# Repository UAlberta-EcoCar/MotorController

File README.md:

# MotorController
## gitignore
* Ignoring board, schematic files

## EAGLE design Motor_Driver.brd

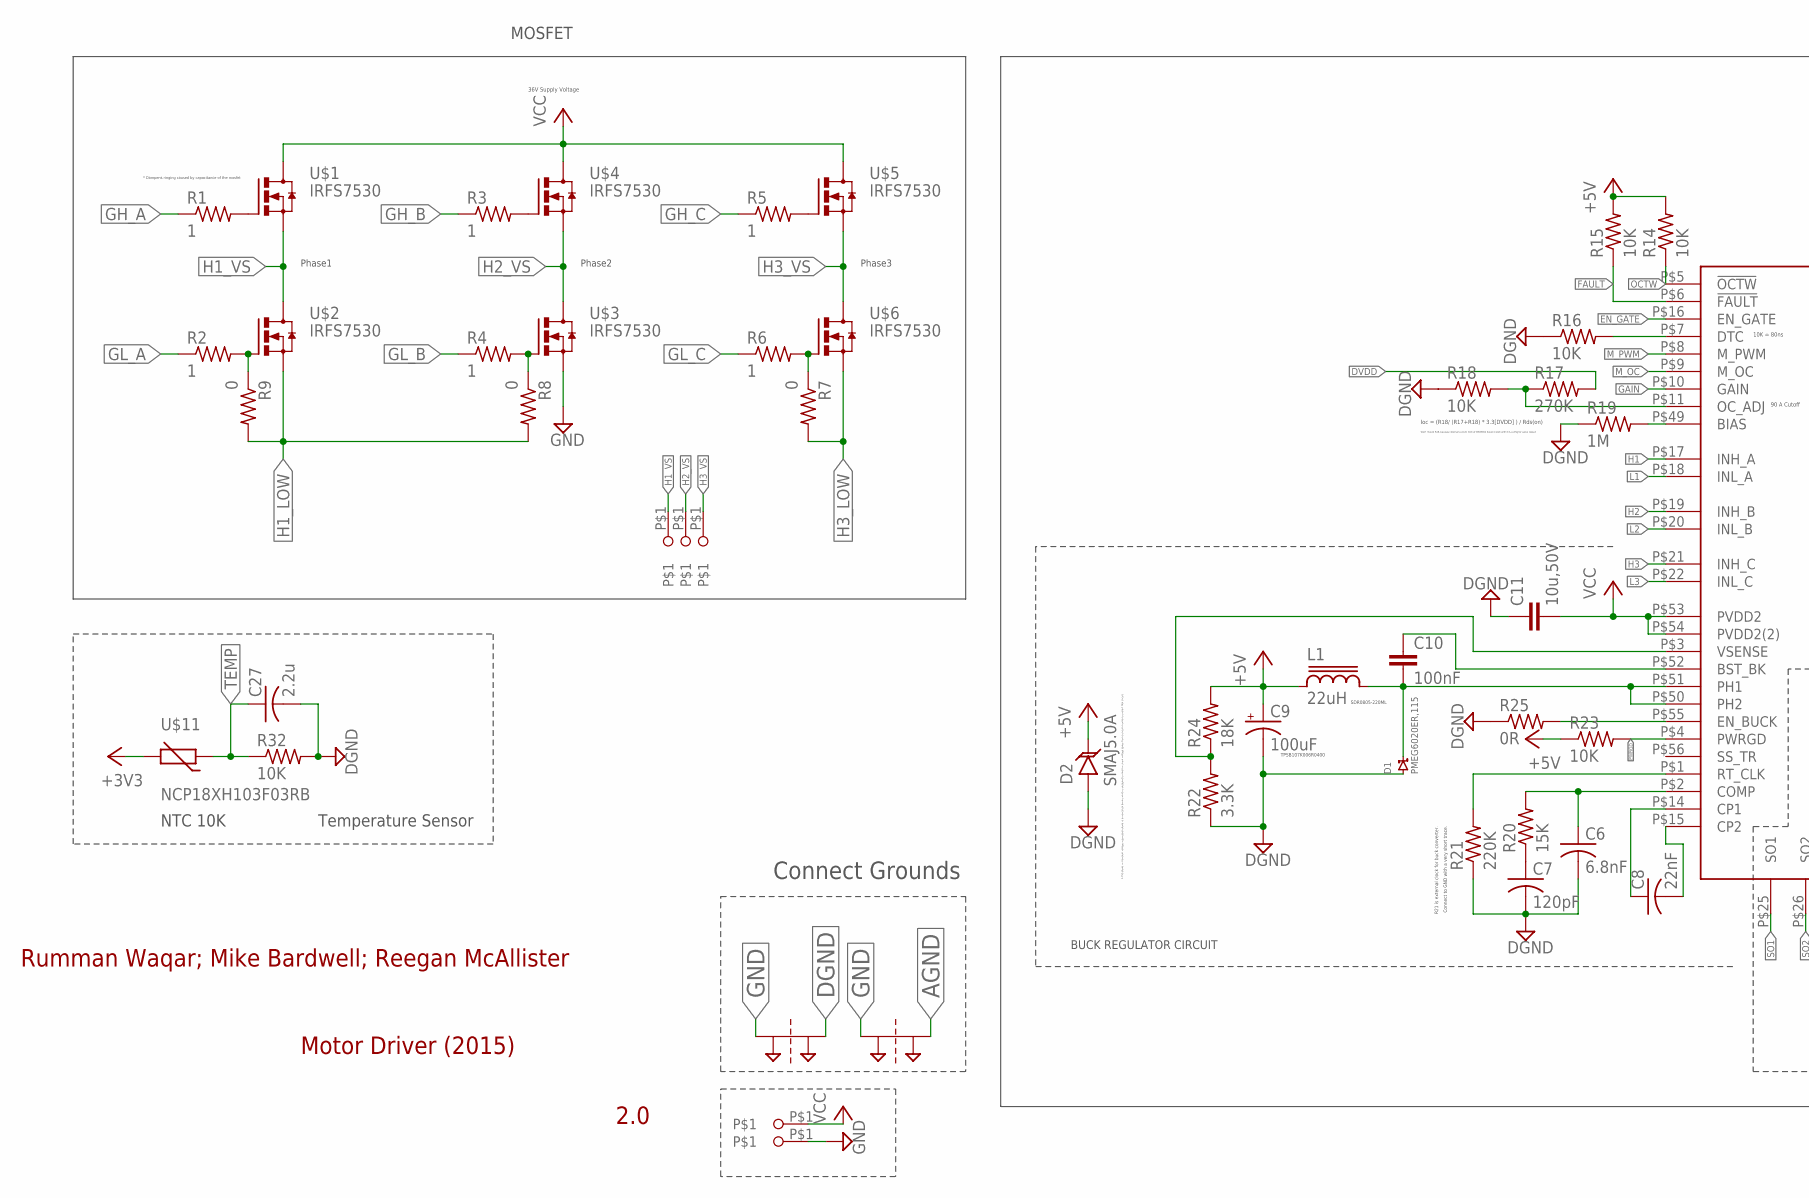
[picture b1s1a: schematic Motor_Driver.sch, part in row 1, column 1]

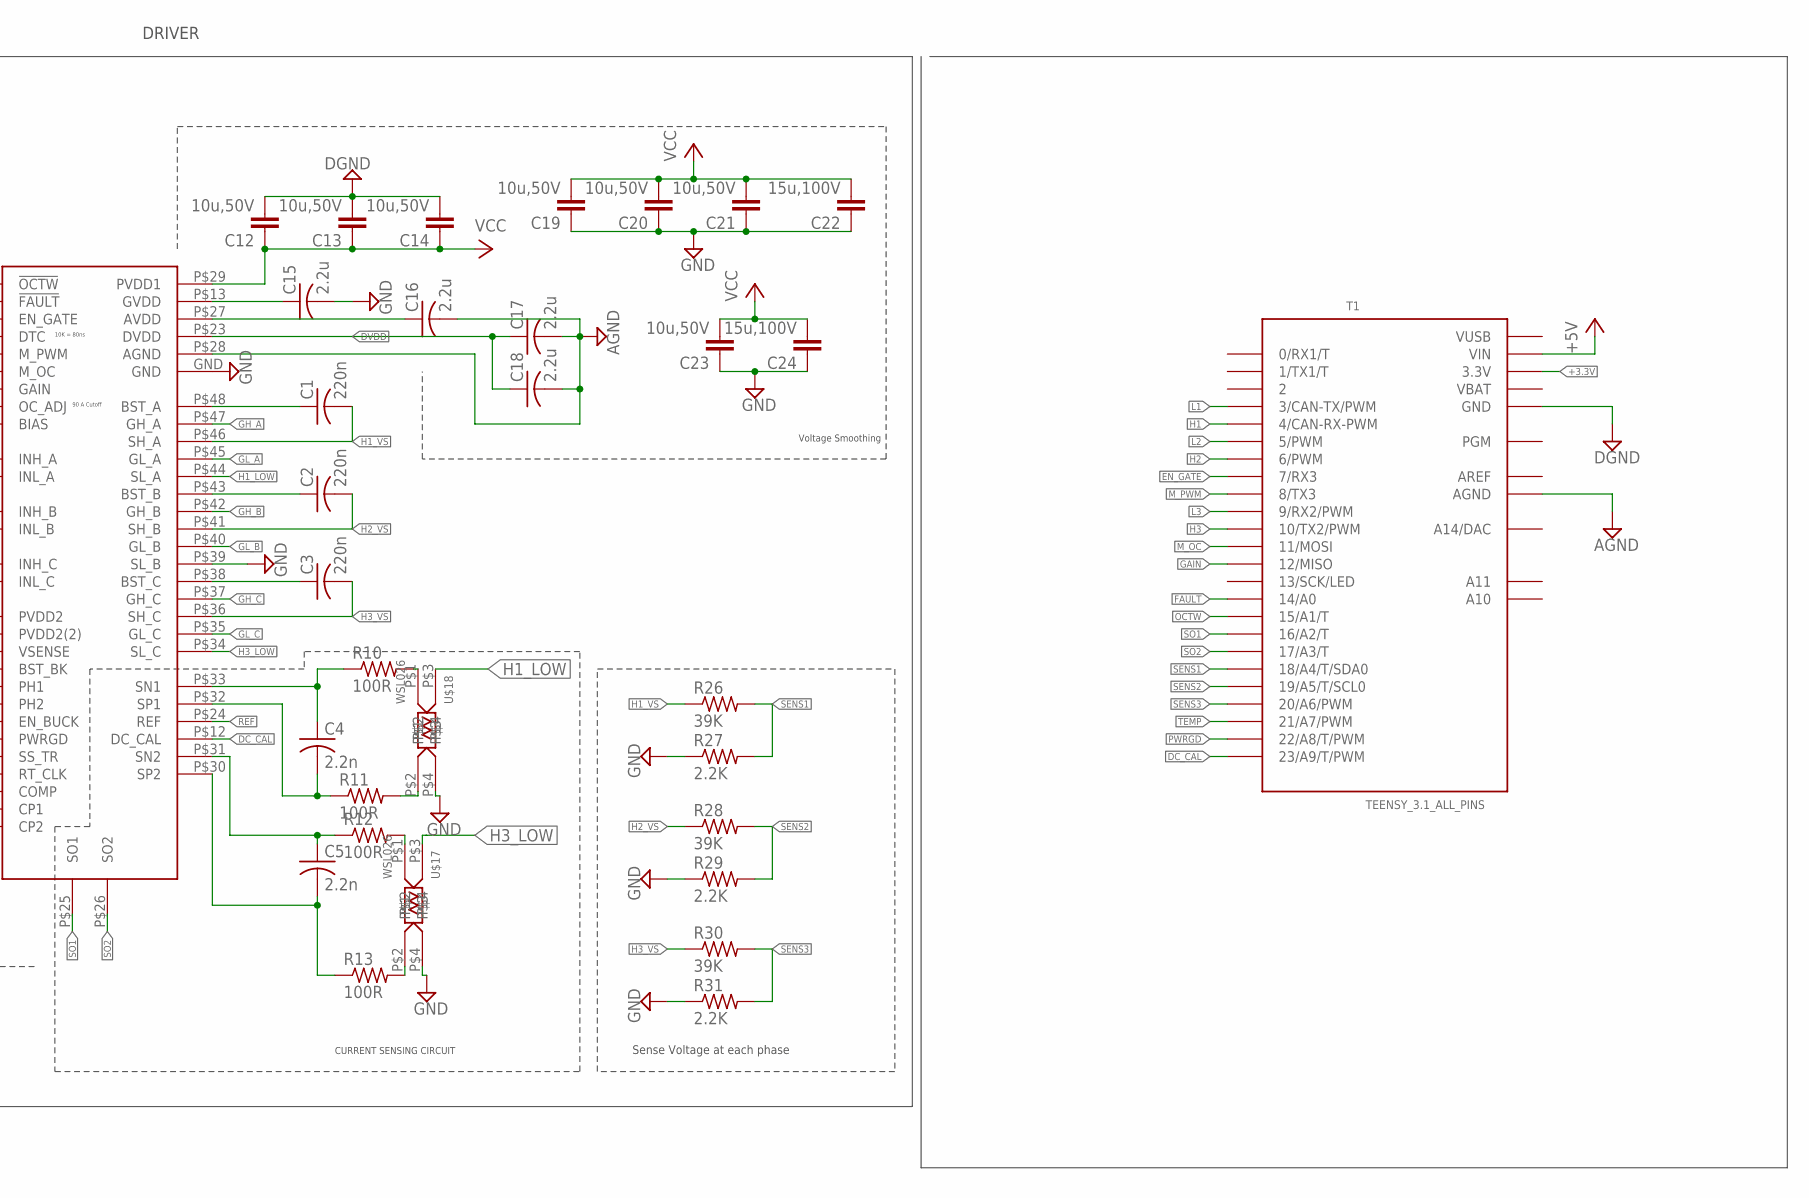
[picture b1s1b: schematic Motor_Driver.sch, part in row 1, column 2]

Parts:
C1, C2, C3: 220n; C0805
C4, C5: 2.2n; C0603
C6: 6.8nF; C0603
C7: 120pF; C0603
C8: 22nF; C0603
C9: 100uF; EIA3528-KIT
C10: 100nF; 0805
C11, C12, C13, C14, C19, C20, C21, C23: 10u,50V; 1206
C15, C16, C17, C18, C27: 2.2u; C0805
C22, C24: 15u,100V; C2220K
D1: PMEG6020ER,115; SOD123W
D2: SMAJ5.0A; SMA-DIODE
L1: 22uH; SDR0805
PT1, PT2: 2PT_GND_TIE
R1, R2, R3, R4, R5, R6: 1; R0603
R7, R8, R9: 0; R0603
R10, R11, R12, R13: 100R; R0603
R14, R15, R16, R18, R23: 10K; R0603
R17: 270K; R0603
R19: 1M; R0603
R20: 15K; R0603
R21: 220K; R0603
R22: 3.3K; R0603
R24: 18K; R0603
R25: 0R; R0603
R26, R28, R30: 39K; R0805
R27, R29, R31: 2.2K; R0805
R32: 10K; M0805
T1: TEENSY_3.1_ALL_PINS; TEENSY3-ALL_PINS
U$1, U$2, U$3, U$4, U$5, U$6: IRFS7530; IRF7530_HEATSINK
U$7: DRV8302
U$11: NCP18XH103F03RB; R0603
U$12, U$13, U$14, U$15, U$16: 1CONN_SOLDER; 1CONN_PAD
U$17, U$18: WSL026; REEL

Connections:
+3.3V: T1.3.3V, T1.3.3V1 (3.3V)
+3V3: U$11.2
+5V: C9.A (+), D2.C, L1.1, R14.2, R15.2, R23.1, R24.2, T1.VIN
AGND: C16.2, C17.2, C18.2, PT2.P$2, T1.AGND, U$7.P$28 (AGND)
AREF: T1.AREF
DC_CAL: T1.23/A9 (23/A9/T/PWM), U$7.P$12 (DC_CAL)
DGND: C6.2, C7.2, C9.C (-), C11.1, C12.2, C13.2, C14.2, C27.2, D1.P$1 (1), D2.A, PT1.P$2, R16.1, R18.1, R19.1, R21.1, R22.1, R25.1, R32.2, T1.GND, T1.GND1 (GND)
DVDD: C17.1, C18.1, R17.2, U$7.P$23 (DVDD)
EN_GATE: T1.7 (7/RX3), U$7.P$16 (EN_GATE)
FAULT: R15.1, T1.14/A0, U$7.P$6 (!FAULT)
GAIN: T1.12 (12/MISO), U$7.P$10 (GAIN)
GH_A: R1.1, U$7.P$47 (GH_A)
GH_B: R3.1, U$7.P$42 (GH_B)
GH_C: R5.1, U$7.P$37 (GH_C)
GL_A: R2.1, U$7.P$45 (GL_A)
GL_B: R4.1, U$7.P$40 (GL_B)
GL_C: R6.1, U$7.P$35 (GL_C)
GND: C15.2, C19.1, C20.1, C21.1, C22.1, C23.1, C24.1, PT1.P$1, PT2.P$1, R27.1, R29.1, R31.1, U$3.S1 (S), U$3.S2 (S), U$3.S3 (S), U$3.S4 (S), U$3.S5 (S), U$7.GND, U$7.P$39 (SL_B), U$16.P$1, U$17.P$4, U$18.P$4
H1: T1.4 (4/CAN-RX-PWM), U$7.P$17 (INH_A)
H1_LOW: R8.2, R9.2, U$2.S1 (S), U$2.S2 (S), U$2.S3 (S), U$2.S4 (S), U$2.S5 (S), U$7.P$44 (SL_A), U$18.P$3
H1_VS: C1.2, R26.1, U$1.S1 (S), U$1.S2 (S), U$1.S3 (S), U$1.S4 (S), U$1.S5 (S), U$2.D1 (D), U$7.P$46 (SH_A), U$14.P$1
H2: T1.6 (6/PWM), U$7.P$19 (INH_B)
H2_VS: C2.2, R28.1, U$3.D1 (D), U$4.S1 (S), U$4.S2 (S), U$4.S3 (S), U$4.S4 (S), U$4.S5 (S), U$7.P$41 (SH_B), U$13.P$1
H3: T1.10 (10/TX2/PWM), U$7.P$21 (INH_C)
H3_LOW: R7.2, U$6.S1 (S), U$6.S2 (S), U$6.S3 (S), U$6.S4 (S), U$6.S5 (S), U$7.P$34 (SL_C), U$17.P$3
H3_VS: C3.2, R30.1, U$5.S1 (S), U$5.S2 (S), U$5.S3 (S), U$5.S4 (S), U$5.S5 (S), U$6.D1 (D), U$7.P$36 (SH_C), U$12.P$1
L1: T1.3 (3/CAN-TX/PWM), U$7.P$18 (INL_A)
L2: T1.5 (5/PWM), U$7.P$20 (INL_B)
L3: T1.9 (9/RX2/PWM), U$7.P$22 (INL_C)
M_OC: T1.11 (11/MOSI), U$7.P$9 (M_OC)
M_PWM: T1.8 (8/TX3), U$7.P$8 (M_PWM)
unnamed: R1.2, U$1.G1 (G)
unnamed: R2.2, R9.1, U$2.G1 (G)
unnamed: R4.2, R8.1, U$3.G1 (G)
unnamed: R3.2, U$4.G1 (G)
unnamed: R5.2, U$5.G1 (G)
unnamed: R6.2, R7.1, U$6.G1 (G)
unnamed: C1.1, U$7.P$48 (BST_A)
unnamed: R17.1, R18.2, U$7.P$11 (OC_ADJ)
unnamed: R10.2, U$18.P$1
unnamed: C8.1, U$7.P$14 (CP1)
unnamed: C5.2, R13.1, U$7.P$30 (SP2)
unnamed: C2.1, U$7.P$43 (BST_B)
unnamed: C8.2, U$7.P$15 (CP2)
unnamed: C7.1, R20.1
unnamed: R21.2, U$7.P$1 (RT_CLK)
unnamed: R16.2, U$7.P$7 (DTC)
unnamed: R25.2, U$7.P$55 (EN_BUCK)
unnamed: C15.1, U$7.P$13 (GVDD)
unnamed: C10.2, D1.P$2 (2), L1.2, U$7.P$50 (PH2), U$7.P$51 (PH1)
unnamed: C6.1, R20.2, U$7.P$2 (COMP)
unnamed: R19.2, U$7.P$49 (BIAS)
unnamed: C4.1, R10.1, U$7.P$33 (SN1)
unnamed: C4.2, R11.1, U$7.P$32 (SP1)
unnamed: C5.1, R12.1, U$7.P$31 (SN2)
unnamed: R12.2, U$17.P$1
unnamed: C3.1, U$7.P$38 (BST_C)
unnamed: C16.1, U$7.P$27 (AVDD)
unnamed: R22.2, R24.1, U$7.P$3 (VSENSE)
unnamed: C10.1, U$7.P$52 (BST_BK)
unnamed: R13.2, U$17.P$2
unnamed: R11.2, U$18.P$2
OCTW: R14.1, T1.15/A1 (15/A1/T), U$7.P$5 (!OCTW)
PWRGD: R23.2, T1.22/A8 (22/A8/T/PWM), U$7.P$4 (PWRGD)
REF: U$7.P$24 (REF)
SENS1: R26.2, R27.2, T1.18/A4 (18/A4/T/SDA0)
SENS2: R28.2, R29.2, T1.19/A5 (19/A5/T/SCL0)
SENS3: R30.2, R31.2, T1.20/A6 (20/A6/PWM)
SO1: T1.16/A2 (16/A2/T), U$7.P$25 (SO1)
SO2: T1.17/A3 (17/A3/T), U$7.P$26 (SO2)
TEMP: C27.1, R32.1, T1.21/A7 (21/A7/PWM), U$11.1
VBAT: T1.VBAT
VCC: C11.2, C12.1, C13.1, C14.1, C19.2, C20.2, C21.2, C22.2, C23.2, C24.2, U$1.D1 (D), U$4.D1 (D), U$5.D1 (D), U$7.P$29 (PVDD1), U$7.P$53 (PVDD2), U$7.P$54 (PVDD2(2)), U$15.P$1
VUSB: T1.VUSB

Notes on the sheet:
* Dampens ringing caused by capacitance of the mosfet
36V Supply Voltage
Phase1
Phase2
Phase3
MOSFET
CURRENT SENSING CIRCUIT
10K = 80ns
Ioc = (R18/ (R17+R18) * 3.3[DVDD] ) / Rds(on)
90 A Cutoff
R21 is external clock for buck converter.
Connect to GND with a very short trace.
SDR0805-220ML
TPSB107K006R0400
A TVS diode, or transient voltage suppression diode, is an electrical device which is designed to divert or shunt voltage spikes from a circuit in order to protect that circuit.
BUCK REGULATOR CIRCUIT
Don't mount R18, because internal current limit of DRV8302 doesn't work with this config for some reason
Voltage Smoothing
Sense Voltage at each phase
DRIVER
Rumman Waqar; Mike Bardwell; Reegan McAllister
Motor Driver (2015)
2.0
Connect Grounds
NTC 10K
Temperature Sensor

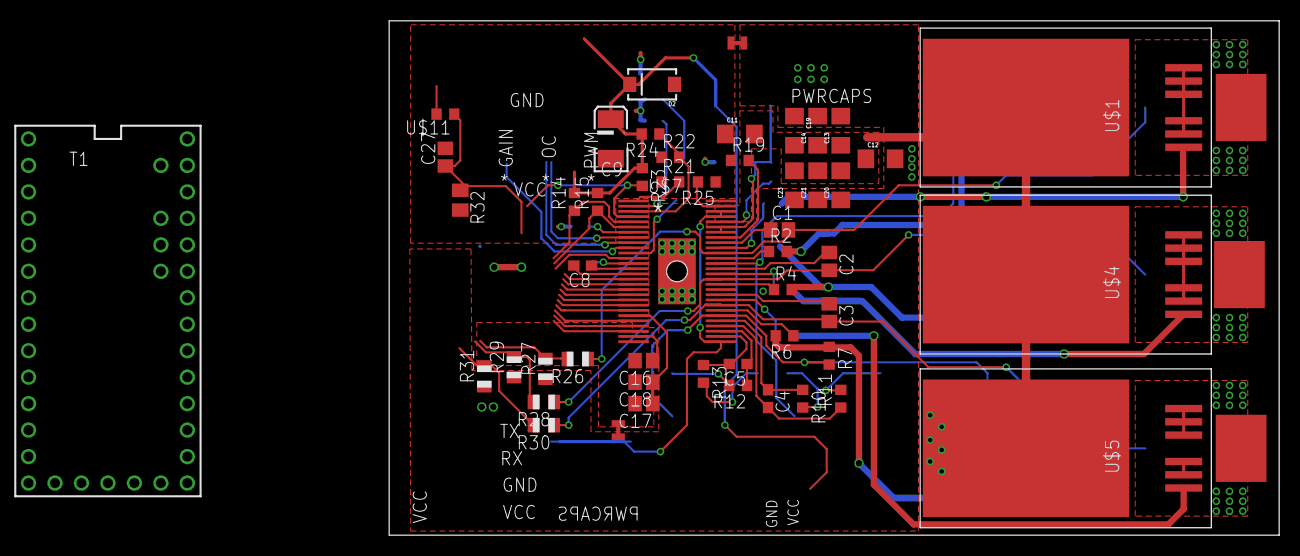
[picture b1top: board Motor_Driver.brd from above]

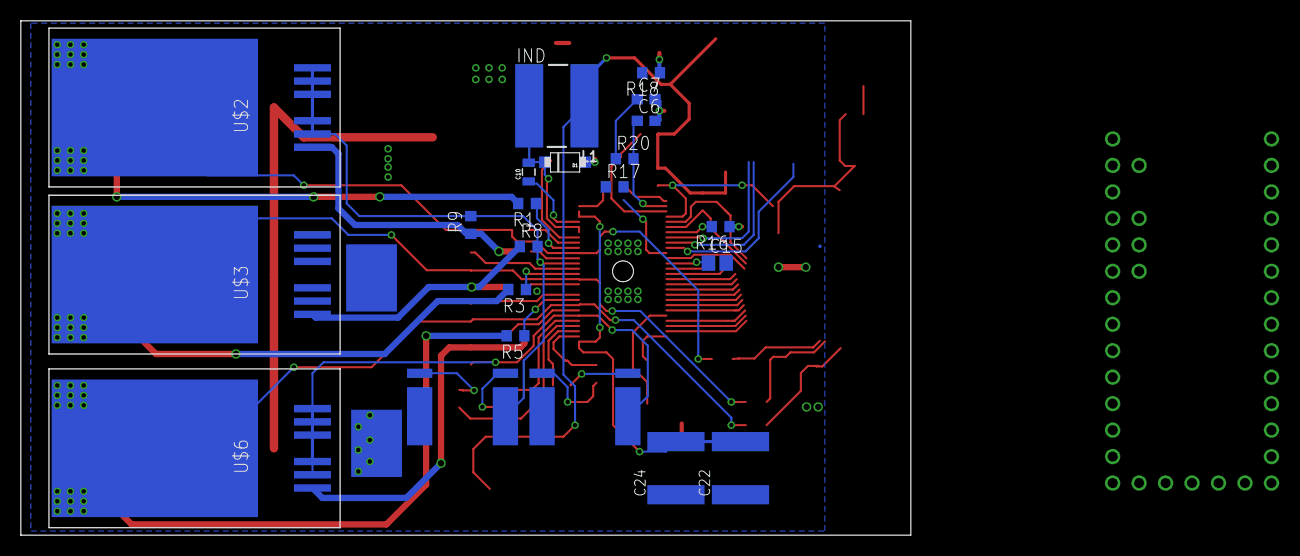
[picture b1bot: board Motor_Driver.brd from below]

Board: 2 copper layers, 85.4 x 49.4 mm, 78 parts (24 on the bottom side), 69 nets.

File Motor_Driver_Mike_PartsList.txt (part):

Partlist exported from C:/Users/Michael/Documents/GitHub/MotorController/Motor_Driver_Mike.sch at 2015-10-31 11:45:45 AM

Part Value           Device                 Package          Description                                           MF    MPN        OC_FARNELL OC_NEWARK
C1   220n            C-USC0805              C0805            CAPACITOR, American symbol                                                                 
C2   220n            C-USC0805              C0805            CAPACITOR, American symbol                                                                 
C3   220n            C-USC0805              C0805            CAPACITOR, American symbol                                                                 
C4   2.2n            C-USC0603              C0603            CAPACITOR, American symbol                                                                 
C5   2.2n            C-USC0603              C0603            CAPACITOR, American symbol                                                                 
C6   6.8nF           C-USC0603              C0603            CAPACITOR, American symbol                                                                 
C7   120pF           C-USC0603              C0603            CAPACITOR, American symbol                                                                 
C8   22nF            C-USC0603              C0603            CAPACITOR, American symbol                                                                 
C9   100uF           CAP_POL3528-KIT        EIA3528-KIT      Capacitor Polarized                                                                        
C10  100nF           CAP0805                0805             Capacitor                                                                                  
C11  10u,50V         CAP1206                1206             Capacitor                                                                                  
C12  10u,50V         CAP1206                1206             Capacitor                                                                                  
C13  10u,50V         CAP1206                1206             Capacitor                                                                                  
C14  10u,50V         CAP1206                1206             Capacitor                                                                                  
C15  2.2u            C-USC0805              C0805            CAPACITOR, American symbol                                                                 
C16  2.2u            C-USC0805              C0805            CAPACITOR, American symbol                                                                 
C17  2.2u            C-USC0805              C0805            CAPACITOR, American symbol                                                                 
C18  2.2u            C-USC0805              C0805            CAPACITOR, American symbol                                                                 
C19  10u,50V         CAP1206                1206             Capacitor                                                                                  
C20  10u,50V         CAP1206                1206             Capacitor                                                                                  
C21  10u,50V         CAP1206                1206             Capacitor                                                                                  
C22  15u,100V        C-EUC2220K             C2220K           CAPACITOR, European symbol                                                                 
C23  10u,50V         CAP1206                1206             Capacitor                                                                                  
C24  15u,100V        C-EUC2220K             C2220K           CAPACITOR, European symbol                                                                 
C25  2.2u            C-USC0805              C0805            CAPACITOR, American symbol                            UMK212BB7225KG-T                                     
C26  100uF           CAP_POL3528-KIT        EIA3528-KIT      Capacitor Polarized                                   478-3528-1-ND                                     
C27  2.2u            C-USC0805              C0805            CAPACITOR, American symbol                            UMK212BB7225KG-T                                      
CTRL 22-23-2041      22-23-2041             22-23-2041       .100" (2.54mm) Center Header - 4 Pin                  MOLEX 22-23-2041 1462920    38C0355  
CURR 22-23-2051      22-23-2051             22-23-2051       .100" (2.54mm) Center Header - 5 Pin                  MOLEX 22-23-2051 1462952    38C9178  
D1   PMEG6020ER,115  DIODE[SCHOTKY]-SOD123W SOD123W                                                                                                     
D2   SMAJ5.0A        TVSSMA                 SMA-DIODE        Transient voltage suppressor- prevents ESD on inputs.                                      
JP2  M_PWM           PINHD-1X3              1X03             PIN HEADER                                                                                 
JP3  M_OC            PINHD-1X3              1X03             PIN HEADER                                                                                 
JP4  GAIN            PINHD-1X3              1X03             PIN HEADER                                                                                 
L1   22uH            SDR0805                SDR0805          POWER INDUCTOR                                                                             
M    22-23-2081      22-23-2081             22-23-2081       .100" (2.54mm) Center Header - 8 Pin                  MOLEX 22-23-2081 1756826    01C7592  
PT1  2PT_GND_TIE     2PT_GND_TIE            2PT_GND_TIE      Package for connecting two ground nets in one place.                                       
PT2  2PT_GND_TIE     2PT_GND_TIE            2PT_GND_TIE      Package for connecting two ground nets in one place.                                       
R1   4.7K            R-US_R0603             R0603            RESISTOR, American symbol                             RC0603JR-074K7L                                     
R2   4.7K            R-US_R0603             R0603            RESISTOR, American symbol                             RC0603JR-074K7L                                     
R3   4.7K            R-US_R0603             R0603            RESISTOR, American symbol                             RC0603JR-074K7L                                     
R4   4.7K            R-US_R0603             R0603            RESISTOR, American symbol                             RC0603JR-074K7L                                     
R5   4.7K            R-US_R0603             R0603            RESISTOR, American symbol                             RC0603JR-074K7L                                     
R6   4.7K            R-US_R0603             R0603            RESISTOR, American symbol                             RC0603JR-074K7L                                     
R7   39K             R-US_R0603             R0603            RESISTOR, American symbol                             RC0603JR-0739KL                                     
R8   39K             R-US_R0603             R0603            RESISTOR, American symbol                             RC0603JR-0739KL                                     
R9   39K             R-US_R0603             R0603            RESISTOR, American symbol                             RC0603JR-0739KL                                     
R10  100R            R-US_R0603             R0603            RESISTOR, American symbol                                                                  
R11  100R            R-US_R0603             R0603            RESISTOR, American symbol                                                                  
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
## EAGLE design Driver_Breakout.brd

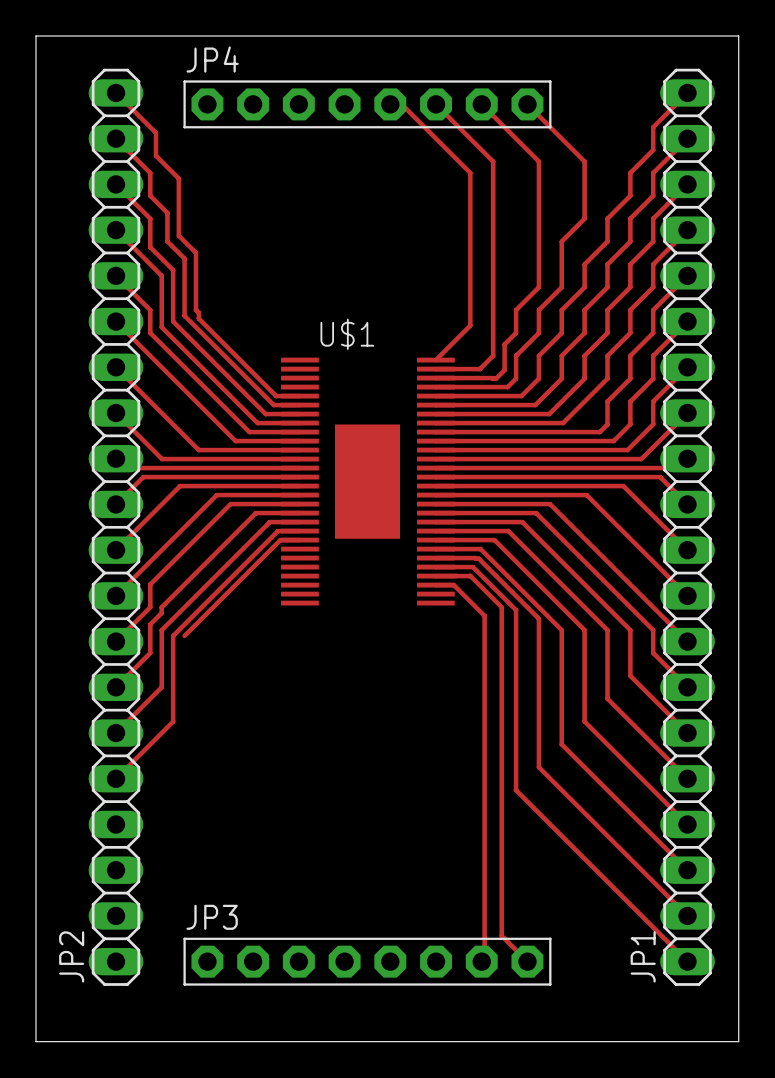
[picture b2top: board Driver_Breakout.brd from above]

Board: 2 copper layers, 39.0 x 55.9 mm, 5 parts (0 on the bottom side), 56 nets.

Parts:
JP1, JP2: 1X20
JP3, JP4: 1X08-BIG
U$1: DRV8302

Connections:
unnamed: JP2.20, U$1.P$5
unnamed: JP2.19, U$1.P$6
unnamed: JP2.18, U$1.P$7
unnamed: JP2.17, U$1.P$8
unnamed: JP2.16, U$1.P$9
unnamed: JP2.15, U$1.P$10
unnamed: JP2.14, U$1.P$11
unnamed: JP2.13, U$1.P$12
unnamed: JP2.12, U$1.P$13
unnamed: JP2.11, U$1.P$14
unnamed: JP2.10, U$1.P$15
unnamed: JP2.9, U$1.P$16
unnamed: JP2.8, U$1.P$17
unnamed: JP2.7, U$1.P$18
unnamed: JP2.6, U$1.P$19
unnamed: JP2.5, U$1.P$20
unnamed: JP2.4, U$1.P$21
unnamed: JP2.3, U$1.P$22
unnamed: JP2.2, U$1.P$23
unnamed: JP2.1, U$1.P$24
unnamed: JP3.1, U$1.P$25
unnamed: JP3.2, U$1.P$26
unnamed: JP4.1, U$1.P$1
unnamed: JP4.2, U$1.P$2
unnamed: JP4.4, U$1.P$4
unnamed: JP4.3, U$1.P$3
unnamed: JP3.3, U$1.P$27
unnamed: JP3.4, U$1.P$28
unnamed: JP4.5, U$1.P$56
unnamed: JP4.6, U$1.P$55
unnamed: JP4.7, U$1.P$54
unnamed: JP4.8, U$1.P$53
unnamed: JP1.20, U$1.P$52
unnamed: JP1.19, U$1.P$51
unnamed: JP1.18, U$1.P$50
unnamed: JP1.17, U$1.P$49
unnamed: JP1.16, U$1.P$48
unnamed: JP1.15, U$1.P$47
unnamed: JP1.14, U$1.P$46
unnamed: JP1.13, U$1.P$45
unnamed: JP1.12, U$1.P$44
unnamed: JP1.11, U$1.P$43
unnamed: JP1.10, U$1.P$42
unnamed: JP1.9, U$1.P$41
unnamed: JP1.8, U$1.P$40
unnamed: JP1.7, U$1.P$39
unnamed: JP1.6, U$1.P$38
unnamed: JP1.5, U$1.P$37
unnamed: JP1.4, U$1.P$36
unnamed: JP1.3, U$1.P$35
unnamed: JP1.2, U$1.P$34
unnamed: JP1.1, U$1.P$33
unnamed: JP3.8, U$1.P$32
unnamed: JP3.7, U$1.P$31
unnamed: JP3.6, U$1.P$30
unnamed: JP3.5, U$1.P$29

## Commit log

2015-10-10 Open board layout challenge to the public
2015-10-11 I got you down to 174 errors
2015-10-17 removed some overlap errors and routed motor board
2015-10-19 did more work routing
2015-10-24 board 2 almost done
2015-10-24 no DRC Errors, 10 airwires
2015-10-24 No DRC Errors, no airwires
2015-10-24 added gitignore
2015-10-31 Populated PartsList.txt with left half of schematic
2015-10-31 Fixed H1_LOW, H3_LOW traces (made them wider and added a polygon around driver for H1_LOW)
2015-11-07 changed board dimensions to get it down to 10 by 10
2016-02-06 Because MiKE fucking forgot to update git
2016-02-07 work damnit
2016-02-09 most updated sch png
2016-02-09 deleted misc
2016-02-09 gerber files for most updated Vedder motor board
2016-02-09 merging blsd_esc repo into Motor_Controller_Hardware and cleaned the files up a bit for uniformities sake. Most updated motor controller versions should be apparent now
2016-02-10 updating verion in repo based on conversations with TI DRV8302
2016-02-13 new board routing, also apparently git works now
2016-02-21 did stuff. So much of stuff
2016-02-22 Updated Git Ignore
2016-02-25 things happened. Board mostly done
2016-03-04 mostly done, w/ initial gerber files
2016-03-08 everything burns
2016-03-08 I don't remember what I'm commiting
2016-03-08 I don't know what this is
2016-03-08 Added silkscreen to top/bottom layer
2016-06-05 SEMA 2016 additions
2016-12-29 switching mcu to teensy 3.2/3.1
2016-12-30 made minor changes starting to route board

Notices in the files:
parts and their libraries:
SparkFun-Passives: Licensing: Creative Commons ShareAlike 4.0 International - https://creativecommons.org/licenses/by-sa/4.0
bourne: Copyright (C) 2008, Bob Starr
